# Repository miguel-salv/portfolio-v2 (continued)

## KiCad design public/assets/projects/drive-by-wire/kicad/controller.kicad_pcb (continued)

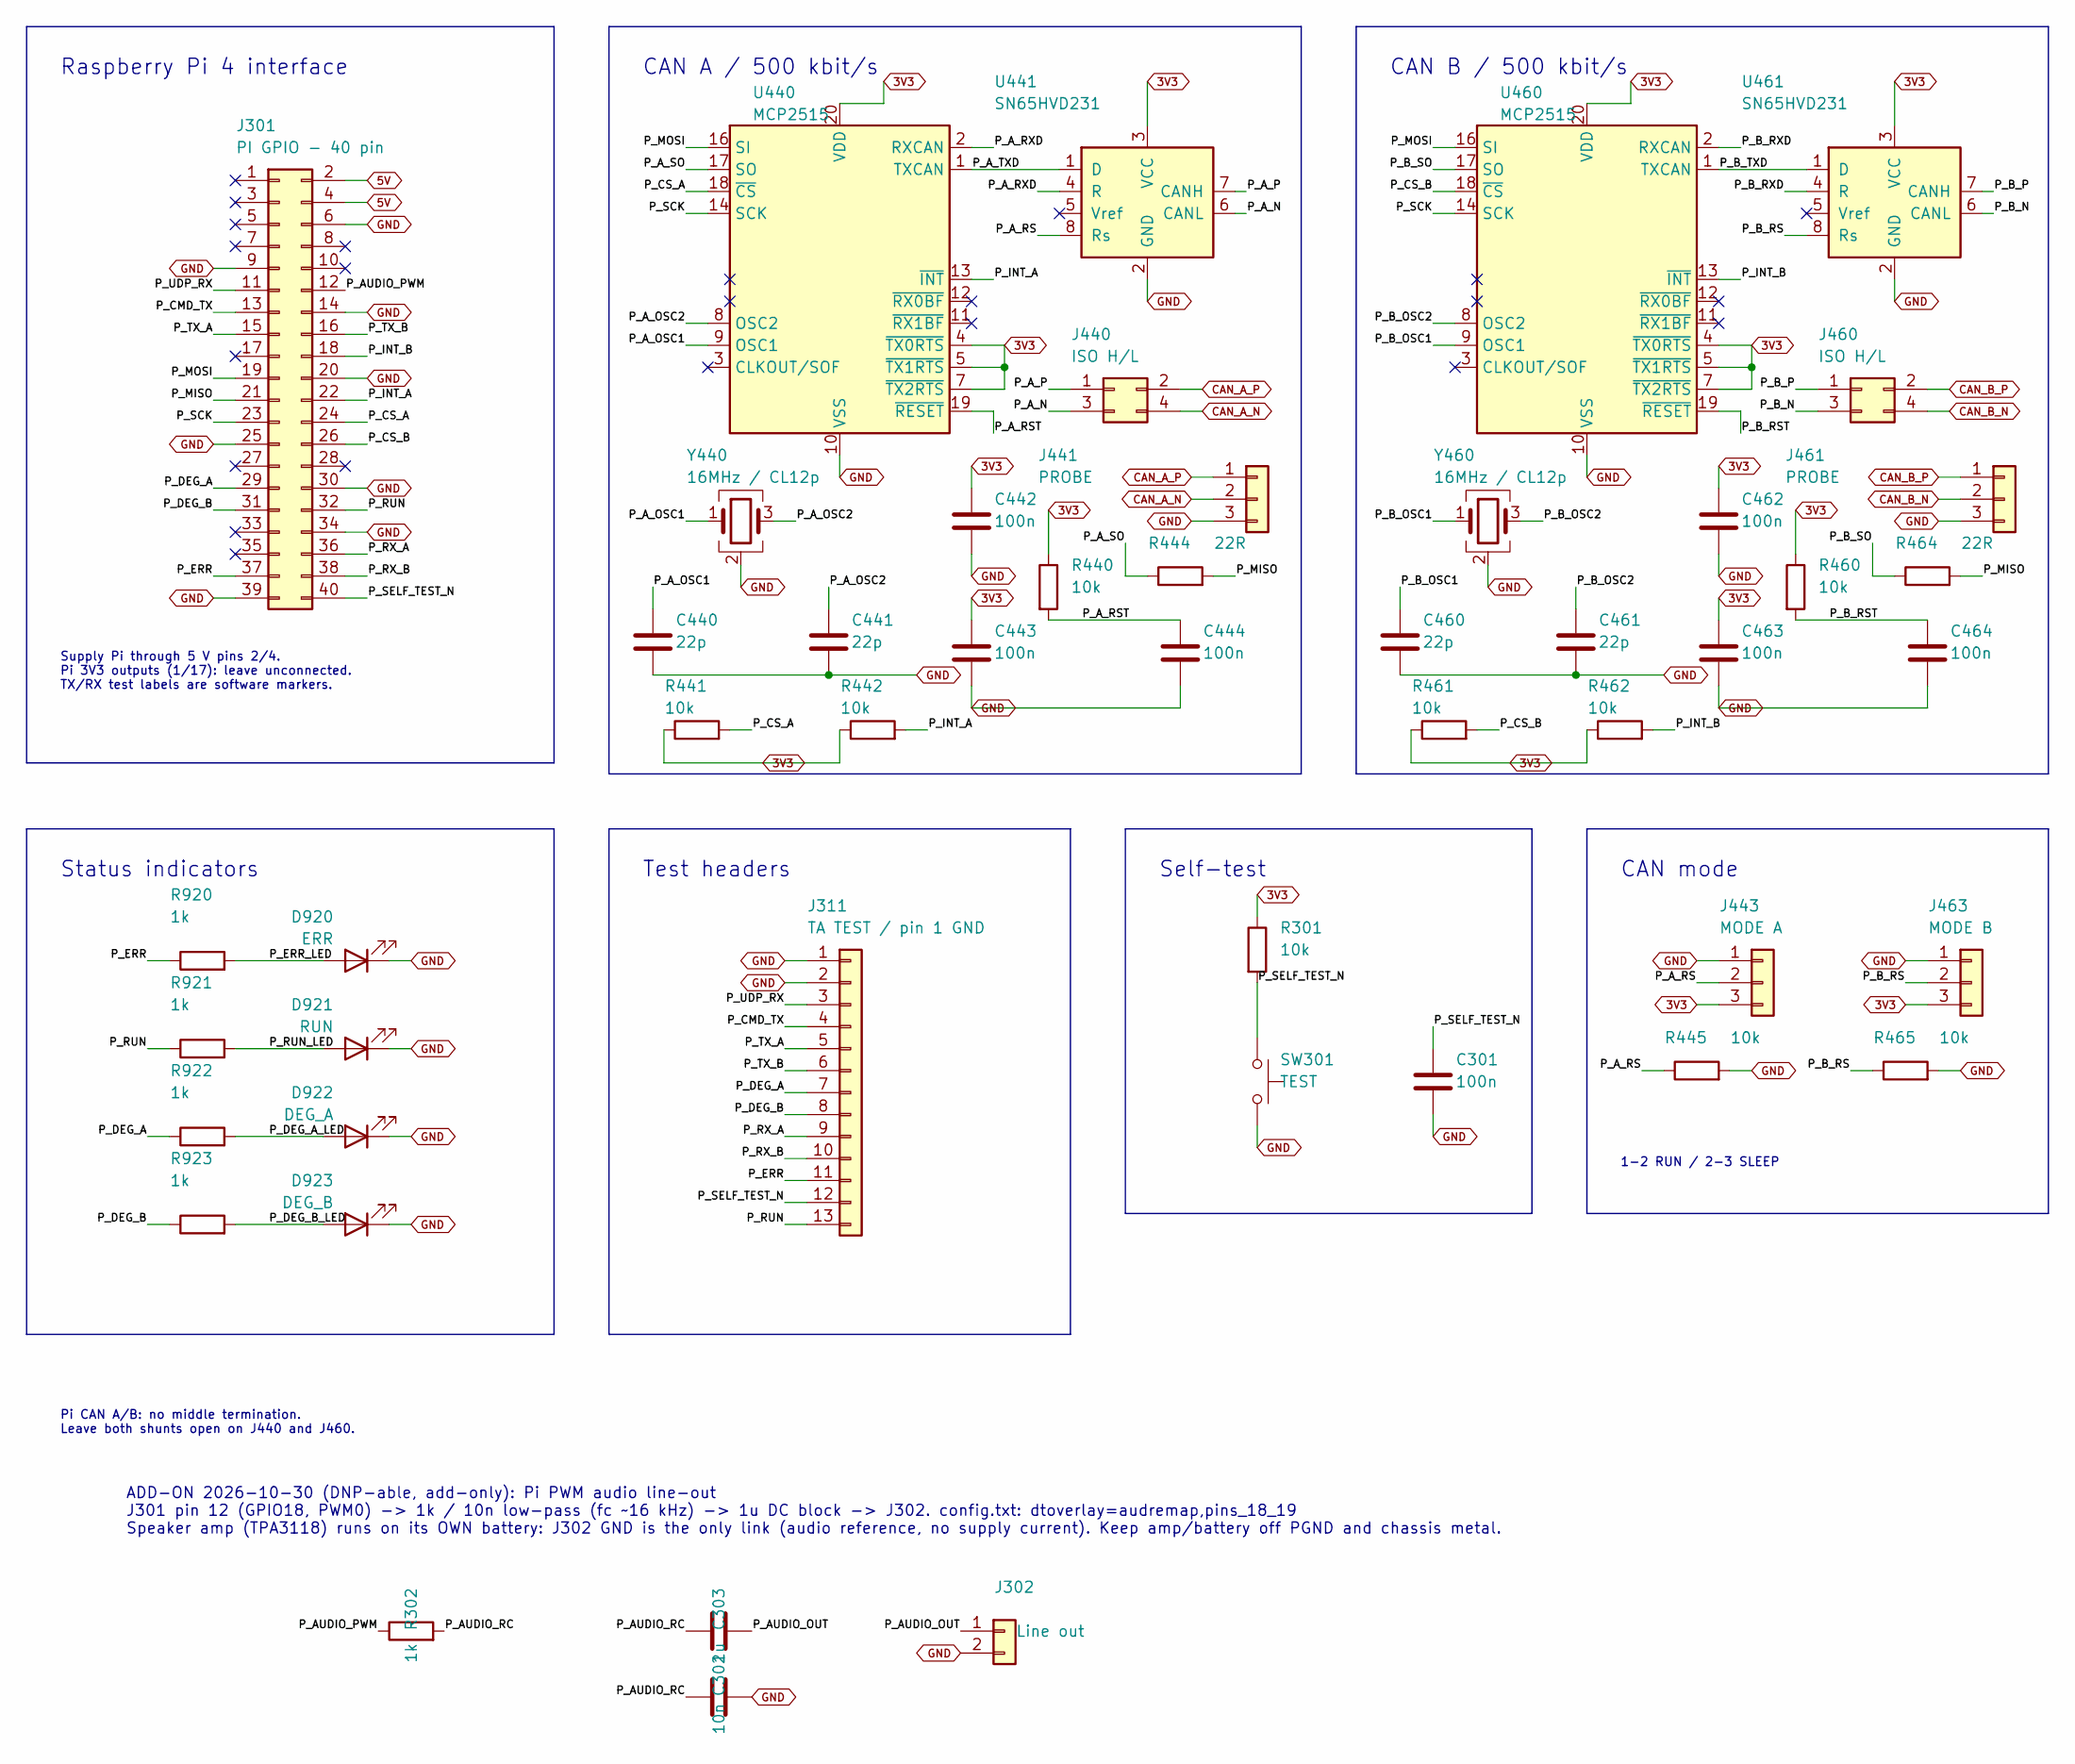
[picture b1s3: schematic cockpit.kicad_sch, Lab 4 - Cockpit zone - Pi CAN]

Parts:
C301, C442, C443, C444, C462, C463, C464: 100n; C_0603_1608Metric; Rating 100n; official v2 stock; 22u/4.7u 0805,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; MPN KGM15AR71C104KT; LCSC N/A - manual / unresolved
C302: 10n; C_0603_1608Metric; Rating PWM audio low-pass C, X7R 50 V; MPN CL10B103KB8NNNC; JLCPCB Class Verify at order
C303: 1u; C_0603_1608Metric; Rating DC block; with ~10k amp input, high-pas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; MPN CL10A105KB8NNNC; JLCPCB Class Verify at order
C440, C441, C460, C461: 22p; C_0603_1608Metric; Rating 22p; official v2 stock; 22u/4.7u 0805, 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; MPN C0603C220J1GACTU; LCSC N/A - manual / unresolved
D920: ERR; LED_0603_1608Metric; Rating 0603; green RUN / red ERR and DEG; MPN LTST-C190KRKT; LCSC N/A - manual / unresolved
D921: RUN; LED_0603_1608Metric; Rating 0603; green RUN / red ERR and DEG; MPN LTST-C190GKT; LCSC N/A - manual / unresolved
D922: DEG_A; LED_0603_1608Metric; Rating 0603; green RUN / red ERR and DEG; MPN LTST-C190KRKT; LCSC N/A - manual / unresolved
D923: DEG_B; LED_0603_1608Metric; Rating 0603; green RUN / red ERR and DEG; MPN LTST-C190KRKT; LCSC N/A - manual / unresolved
J301: PI GPIO - 40 pin; PinHeader_2x20_P2.54mm_Vertical; Rating See footprint and netlist for pin count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; MPN 2.54mm pin header; cut to length; LCSC N/A - manual / unresolved
J302: Line out; PinHeader_1x02_P2.54mm_Vertical; Rating 1 = AUDIO (to amp IN+), 2 = GND (to amp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; MPN 2.54mm pin header 1x02 (cut from strip); JLCPCB Class Verify at order
J311: TA TEST / pin 1 GND; PinHeader_1x13_P2.54mm_Vertical; Rating See footprint and netlist for pin count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; MPN 2.54mm pin header; cut to length; LCSC N/A - manual / unresolved
J440, J460: ISO H/L; PinHeader_2x02_P2.54mm_Vertical; Rating See footprint and netlist for pin count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; MPN 2.54mm pin header; cut to length; LCSC N/A - manual / unresolved
J441, J461: PROBE; PinHeader_1x03_P2.54mm_Vertical; Rating See footprint and netlist for pin count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; MPN 2.54mm pin header; cut to length; LCSC N/A - manual / unresolved
J443: MODE A; PinHeader_1x03_P2.54mm_Vertical; Rating See footprint and netlist for pin count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; MPN 2.54mm pin header; cut to length; LCSC N/A - manual / unresolved
J463: MODE B; PinHeader_1x03_P2.54mm_Vertical; Rating See footprint and netlist for pin count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; MPN 2.54mm pin header; cut to length; LCSC N/A - manual / unresolved
R301, R440, R441, R442, R445, R460, R461, R462, R465: 10k; R_0603_1608Metric; Rating 10k; 0603 0.1W; 22R 5%, others 1%; MPN CRCW060310K0FKEA; LCSC N/A - manual / unresolved
R302: 1k; R_0603_1608Metric; Rating PWM audio low-pass R (with C302: fc = 1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; MPN 0603WAF1001T5E; JLCPCB Class Verify at order
R444, R464: 22R; R_0603_1608Metric; Rating 22R; 0603 0.1W; 22R 5%, others 1%; MPN CRGCQ0603J22R; LCSC N/A - manual / unresolved
R920, R921, R922, R923: 1k; R_0603_1608Metric; Rating 1k; 0603 0.1W; 22R 5%, others 1%; MPN ERJ-3EKF1001V; LCSC N/A - manual / unresolved
SW301: TEST; SW_GCT_SWT0210; Rating Course part, custom two-net footprint v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; MPN SWT0210-045026GSA; LCSC N/A - manual / unresolved
U440, U460: MCP2515; TSSOP-20_4.4x6.5mm_P0.65mm; Rating TSSOP20; 16MHz at 3V3; MPN MCP2515T-I/ST; LCSC C185941
U441, U461: SN65HVD231; SOIC-8_3.9x4.9mm_P1.27mm; Rating SOIC8; Rs mode 1-2 RUN, 2-3 SLEEP. 10k 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; MPN SN65HVD231DR; LCSC C129257
Y440, Y460: 16MHz / CL12p; Crystal_SMD_3225-4Pin_3.2x2.5mm; Rating 16MHz CL12pF 80ohm; 3225 four pads; par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; MPN CX3225SB16000H0FLJCC; LCSC N/A - course stock

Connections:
3V3: C442.1, C443.1, C462.1, C463.1, J443.3, J463.3, R301.1, R440.1, R441.1, R442.1, R460.1, R461.1, R462.1, U440.4 (~TX0RTS), U440.5 (~TX1RTS), U440.7 (~TX2RTS), U440.20 (VDD), U441.3 (VCC), U460.4 (~TX0RTS), U460.5 (~TX1RTS), U460.7 (~TX2RTS), U460.20 (VDD), U461.3 (VCC); also elsewhere on the board
5V: J301.2, J301.4; also elsewhere on the board
/Cockpit zone - Pi CAN/P_AUDIO_OUT: C303.2, J302.1
/Cockpit zone - Pi CAN/P_AUDIO_PWM: J301.12, R302.1
/Cockpit zone - Pi CAN/P_AUDIO_RC: C302.1, C303.1, R302.2
/Cockpit zone - Pi CAN/P_A_N: J440.3, U441.6 (CANL)
/Cockpit zone - Pi CAN/P_A_OSC1: C440.1, U440.9 (OSC1), Y440.1
/Cockpit zone - Pi CAN/P_A_OSC2: C441.1, U440.8 (OSC2), Y440.3
/Cockpit zone - Pi CAN/P_A_P: J440.1, U441.7 (CANH)
/Cockpit zone - Pi CAN/P_A_RS: J443.2, R445.1, U441.8 (Rs)
/Cockpit zone - Pi CAN/P_A_RST: C444.1, R440.2, U440.19 (~RESET)
/Cockpit zone - Pi CAN/P_A_RXD: U440.2 (RXCAN), U441.4 (R)
/Cockpit zone - Pi CAN/P_A_SO: R444.1, U440.17 (SO)
/Cockpit zone - Pi CAN/P_A_TXD: U440.1 (TXCAN), U441.1 (D)
/Cockpit zone - Pi CAN/P_B_N: J460.3, U461.6 (CANL)
/Cockpit zone - Pi CAN/P_B_OSC1: C460.1, U460.9 (OSC1), Y460.1
/Cockpit zone - Pi CAN/P_B_OSC2: C461.1, U460.8 (OSC2), Y460.3
/Cockpit zone - Pi CAN/P_B_P: J460.1, U461.7 (CANH)
/Cockpit zone - Pi CAN/P_B_RS: J463.2, R465.1, U461.8 (Rs)
/Cockpit zone - Pi CAN/P_B_RST: C464.1, R460.2, U460.19 (~RESET)
/Cockpit zone - Pi CAN/P_B_RXD: U460.2 (RXCAN), U461.4 (R)
/Cockpit zone - Pi CAN/P_B_SO: R464.1, U460.17 (SO)
/Cockpit zone - Pi CAN/P_B_TXD: U460.1 (TXCAN), U461.1 (D)
/Cockpit zone - Pi CAN/P_CMD_TX: J301.13, J311.4
/Cockpit zone - Pi CAN/P_CS_A: J301.24, R441.2, U440.18 (~CS)
/Cockpit zone - Pi CAN/P_CS_B: J301.26, R461.2, U460.18 (~CS)
/Cockpit zone - Pi CAN/P_DEG_A: J301.29, J311.7, R922.1
/Cockpit zone - Pi CAN/P_DEG_A_LED: D922.2 (A), R922.2
/Cockpit zone - Pi CAN/P_DEG_B: J301.31, J311.8, R923.1
/Cockpit zone - Pi CAN/P_DEG_B_LED: D923.2 (A), R923.2
/Cockpit zone - Pi CAN/P_ERR: J301.37, J311.11, R920.1
/Cockpit zone - Pi CAN/P_ERR_LED: D920.2 (A), R920.2
/Cockpit zone - Pi CAN/P_INT_A: J301.22, R442.2, U440.13 (~INT)
/Cockpit zone - Pi CAN/P_INT_B: J301.18, R462.2, U460.13 (~INT)
/Cockpit zone - Pi CAN/P_MISO: J301.21, R444.2, R464.2
/Cockpit zone - Pi CAN/P_MOSI: J301.19, U440.16 (SI), U460.16 (SI)
/Cockpit zone - Pi CAN/P_RUN: J301.32, J311.13, R921.1
/Cockpit zone - Pi CAN/P_RUN_LED: D921.2 (A), R921.2
/Cockpit zone - Pi CAN/P_RX_A: J301.36, J311.9
/Cockpit zone - Pi CAN/P_RX_B: J301.38, J311.10
/Cockpit zone - Pi CAN/P_SCK: J301.23, U440.14 (SCK), U460.14 (SCK)
/Cockpit zone - Pi CAN/P_SELF_TEST_N: C301.1, J301.40, J311.12, R301.2, SW301.1
/Cockpit zone - Pi CAN/P_TX_A: J301.15, J311.5
/Cockpit zone - Pi CAN/P_TX_B: J301.16, J311.6
/Cockpit zone - Pi CAN/P_UDP_RX: J301.11, J311.3
CAN_A_N: J440.4, J441.2; also elsewhere on the board
CAN_A_P: J440.2, J441.1; also elsewhere on the board
CAN_B_N: J460.4, J461.2; also elsewhere on the board
CAN_B_P: J460.2, J461.1; also elsewhere on the board
GND: C301.2, C302.2, C440.2, C441.2, C442.2, C443.2, C444.2, C460.2, C461.2, C462.2, C463.2, C464.2, D920.1 (K), D921.1 (K), D922.1 (K), D923.1 (K), J301.6, J301.9, J301.14, J301.20, J301.25, J301.30, J301.34, J301.39, J302.2, J311.1, J311.2, J441.3, J443.1, J461.3, J463.1, R445.2, R465.2, SW301.2, U440.10 (VSS), U441.2 (GND), U460.10 (VSS), U461.2 (GND), Y440.2 (G), Y440.4 (G), Y460.2 (G), Y460.4 (G); also elsewhere on the board

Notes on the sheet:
Test headers
CAN A / 500 kbit/s
Pi CAN A/B: no middle termination. Leave both shunts open on J440 and J460.
1-2 RUN / 2-3 SLEEP
CAN mode
Status indicators
CAN B / 500 kbit/s
Supply Pi through 5 V pins 2/4. Pi 3V3 outputs (1/17): leave unconnected. TX/RX test labels are software markers.
Self-test
Raspberry Pi 4 interface
ADD-ON 2026-10-30 (DNP-able, add-only): Pi PWM audio line-out J301 pin 12 (GPIO18, PWM0) -> 1k / 10n low-pass (fc ~16 kHz) -> 1u DC block -> J302. config.txt: dtoverlay=audremap,pins_18_19 Speaker amp (TPA3118) runs on its OWN battery: J302 GND is the only link (audio reference, no supply current).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

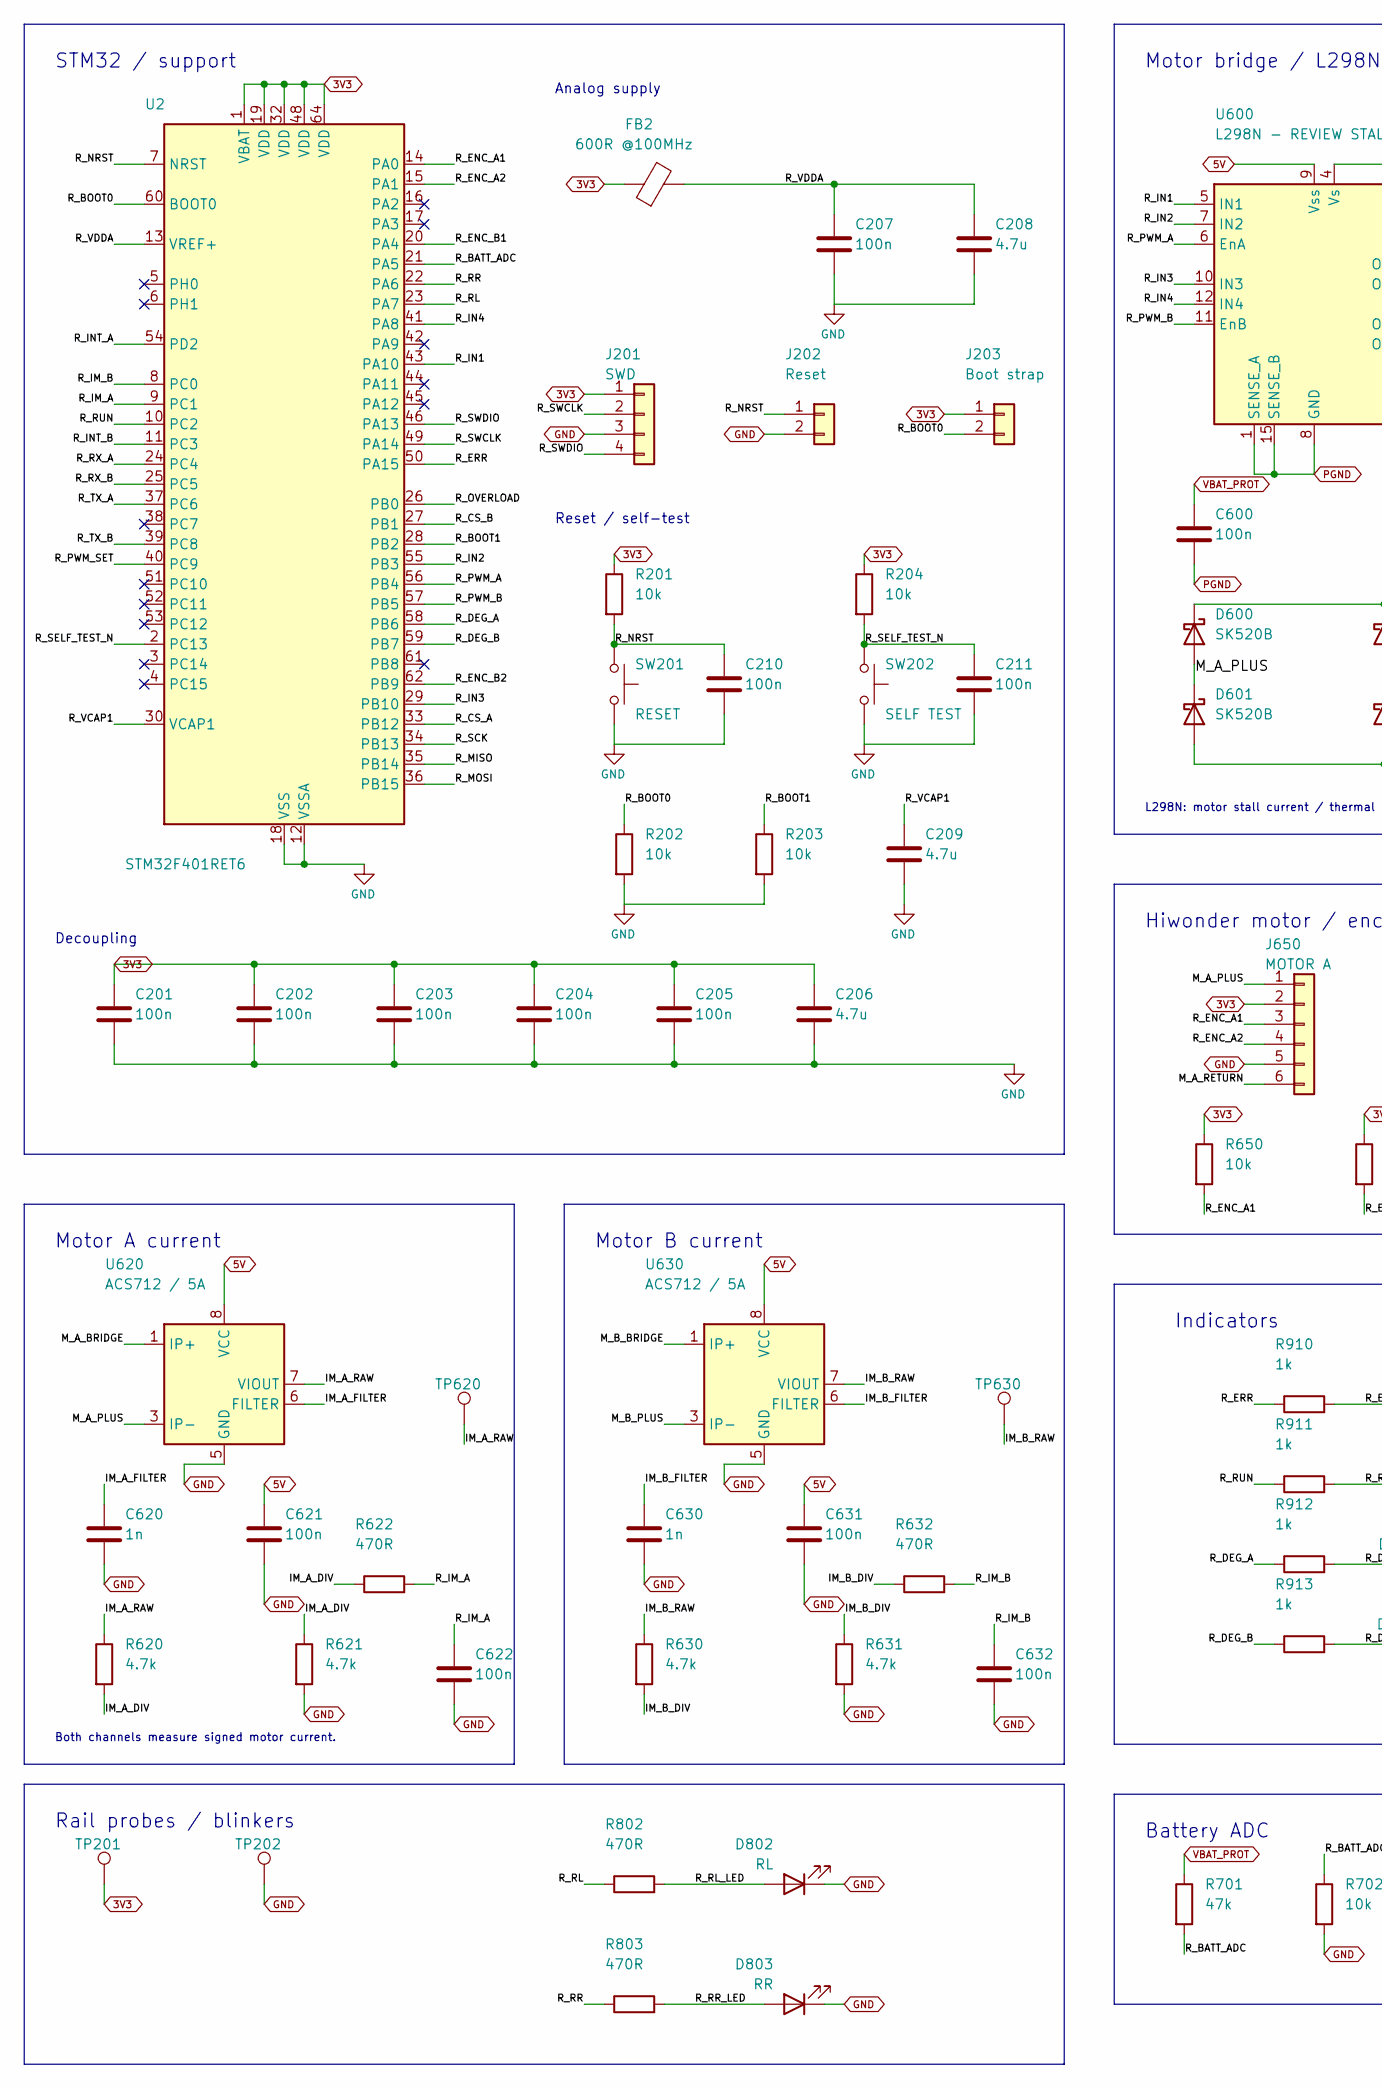
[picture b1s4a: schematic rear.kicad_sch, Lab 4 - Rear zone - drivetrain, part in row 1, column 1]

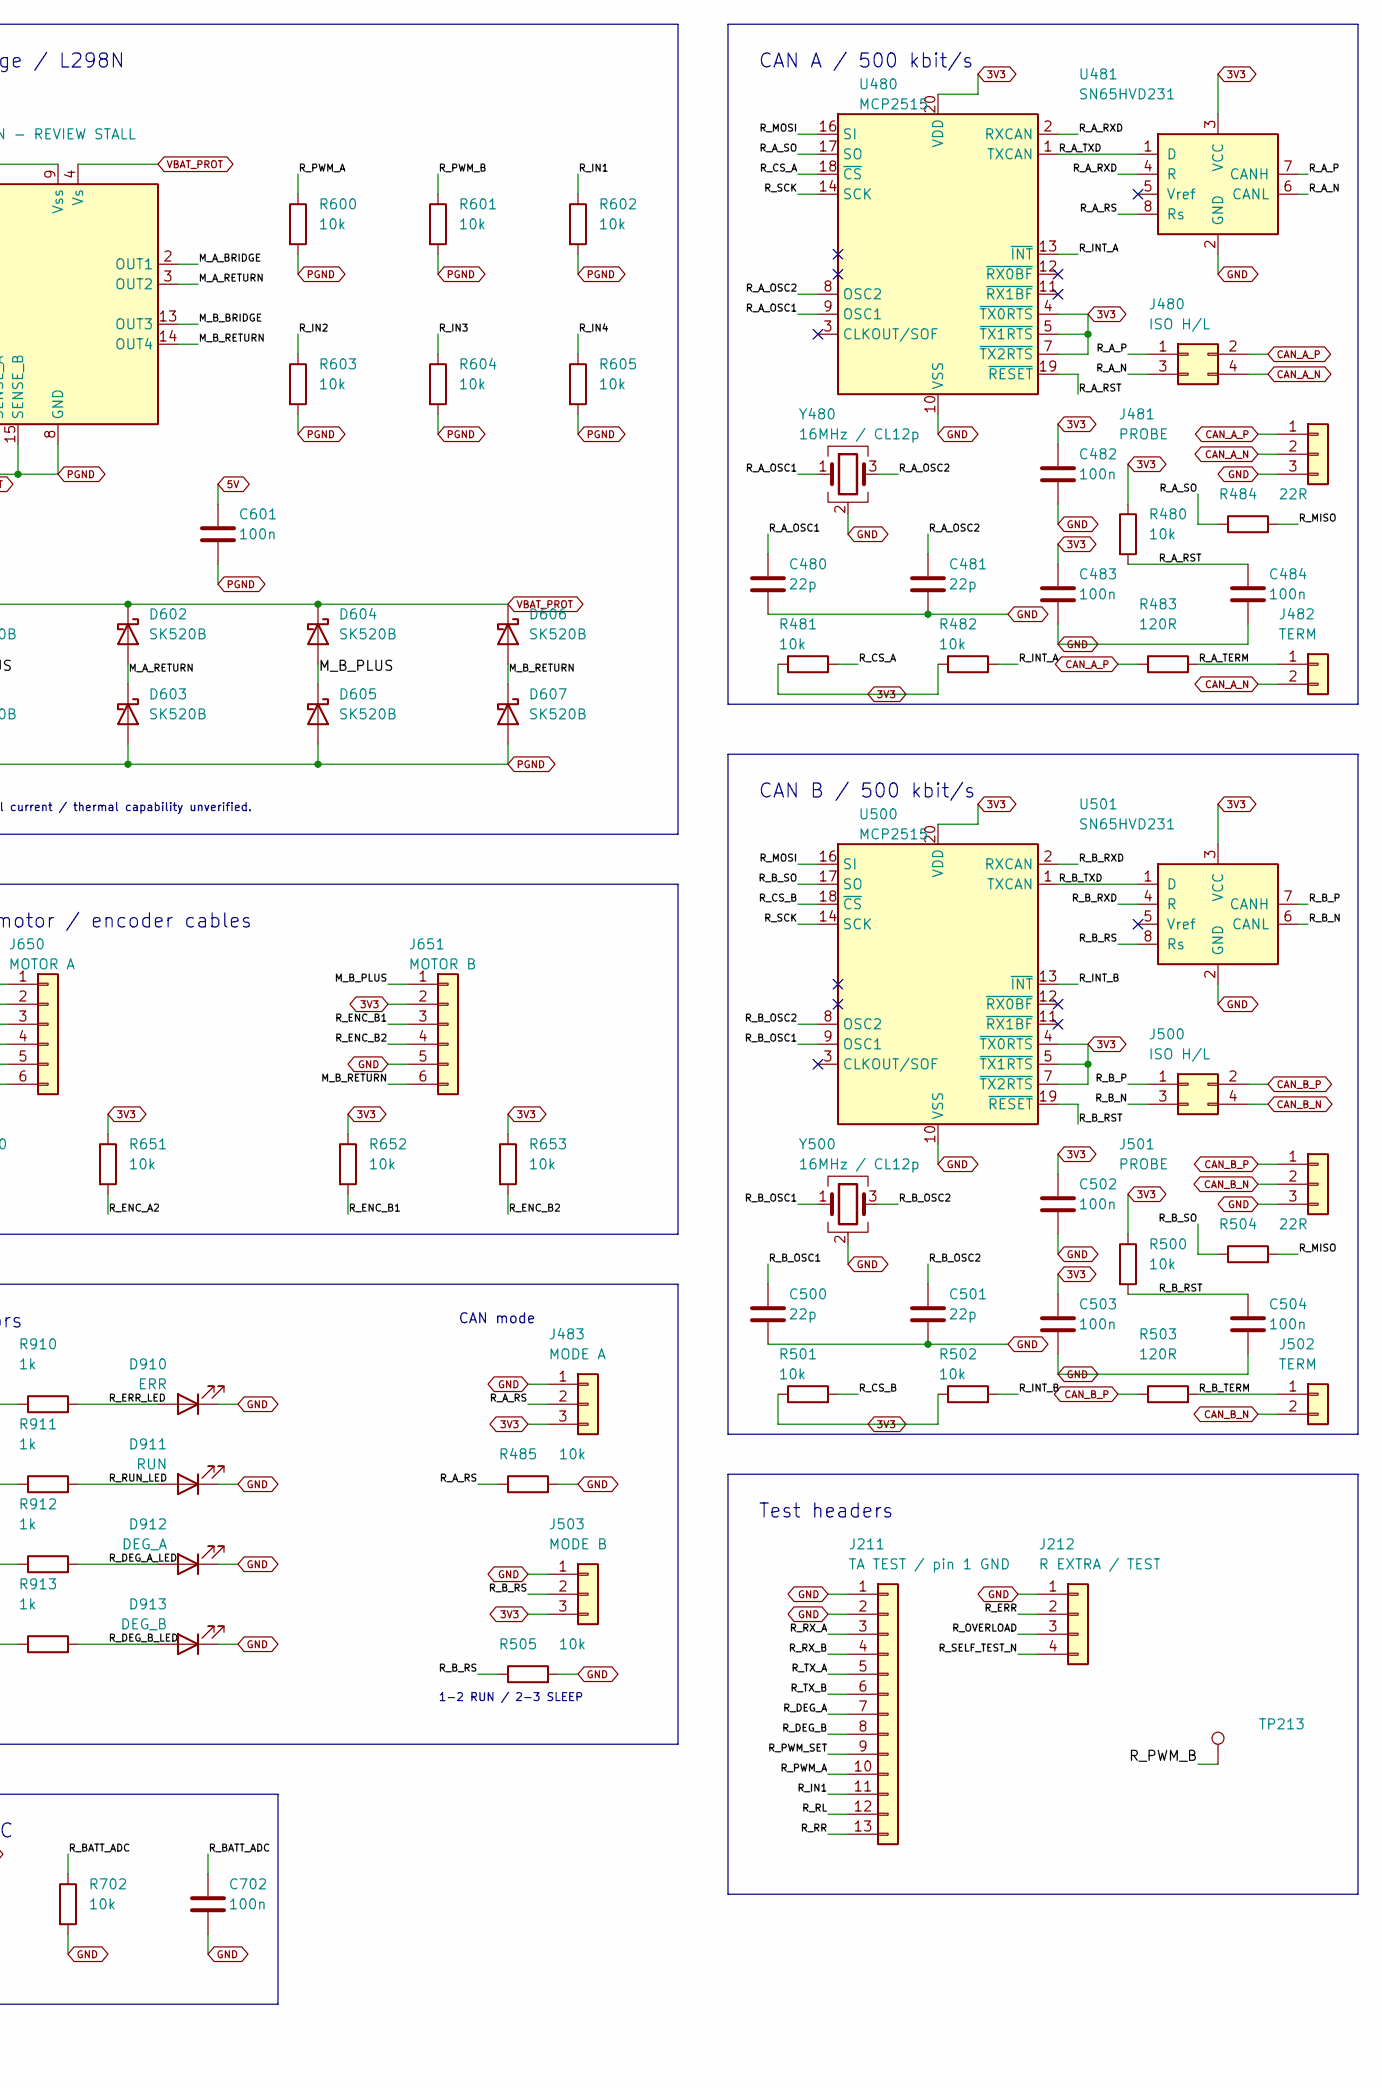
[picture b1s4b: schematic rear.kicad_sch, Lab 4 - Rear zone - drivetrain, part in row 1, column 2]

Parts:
C201, C202, C203, C204, C205, C207, C210, C211, C482, C483, C484, C502, C503, C504, C600, C601, C621, C622, C631, C632, C702: 100n; C_0603_1608Metric; Rating 100n; official v2 stock; 22u/4.7u 0805,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; MPN KGM15AR71C104KT; LCSC N/A - manual / unresolved
C206, C208, C209: 4.7u; C_0805_2012Metric; Rating 4.7u; official v2 stock; 22u/4.7u 0805,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; MPN GRM21BR71C475KE51L; LCSC N/A - manual / unresolved
C480, C481, C500, C501: 22p; C_0603_1608Metric; Rating 22p; official v2 stock; 22u/4.7u 0805, 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; MPN C0603C220J1GACTU; LCSC N/A - manual / unresolved
C620, C630: 1n; C_0603_1608Metric; Rating 1n; official v2 stock; 22u/4.7u 0805, o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; MPN GCM1885C2A102FA16D; LCSC N/A - manual / unresolved
D600, D601, D602, D603, D604, D605, D606, D607: SK520B; D_SMB; Rating 5A 200V SMB; bridge flyback; MPN SK520B; LCSC N/A - manual / unresolved
D802: RL; LED_D3.0mm; Rating Yellow 3mm radial; 470R limits current; MPN 151031YS06000; LCSC N/A - manual / unresolved
D803: RR; LED_D3.0mm; Rating Yellow 3mm radial; 470R limits current; MPN 151031YS06000; LCSC N/A - manual / unresolved
D910: ERR; LED_0603_1608Metric; Rating 0603; green RUN / red ERR and DEG; MPN LTST-C190KRKT; LCSC N/A - manual / unresolved
D911: RUN; LED_0603_1608Metric; Rating 0603; green RUN / red ERR and DEG; MPN LTST-C190GKT; LCSC N/A - manual / unresolved
D912: DEG_A; LED_0603_1608Metric; Rating 0603; green RUN / red ERR and DEG; MPN LTST-C190KRKT; LCSC N/A - manual / unresolved
D913: DEG_B; LED_0603_1608Metric; Rating 0603; green RUN / red ERR and DEG; MPN LTST-C190KRKT; LCSC N/A - manual / unresolved
FB2: 600R @100MHz; L_0603_1608Metric; Rating 0603; 600ohm@100MHz,500mA; 0.35ohm maxD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; MPN 742863160; LCSC N/A - manual / unresolved
J201: SWD; PinHeader_1x04_P2.54mm_Vertical; Rating See footprint and netlist for pin count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; MPN 2.54mm pin header; cut to length; LCSC N/A - manual / unresolved
J202: Reset; PinHeader_1x02_P2.54mm_Vertical; Rating See footprint and netlist for pin count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; MPN 2.54mm pin header; cut to length; LCSC N/A - manual / unresolved
J203: Boot strap; PinHeader_1x02_P2.54mm_Vertical; Rating See footprint and netlist for pin count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; MPN 2.54mm pin header; cut to length; LCSC N/A - manual / unresolved
J211: TA TEST / pin 1 GND; PinHeader_1x13_P2.54mm_Vertical; Rating See footprint and netlist for pin count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; MPN 2.54mm pin header; cut to length; LCSC N/A - manual / unresolved
J212: R EXTRA / TEST; PinHeader_1x04_P2.54mm_Vertical; Rating See footprint and netlist for pin count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; MPN 2.54mm pin header; cut to length; LCSC N/A - manual / unresolved
J480, J500: ISO H/L; PinHeader_2x02_P2.54mm_Vertical; Rating See footprint and netlist for pin count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; MPN 2.54mm pin header; cut to length; LCSC N/A - manual / unresolved
J481, J501: PROBE; PinHeader_1x03_P2.54mm_Vertical; Rating See footprint and netlist for pin count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; MPN 2.54mm pin header; cut to length; LCSC N/A - manual / unresolved
J482, J502: TERM; PinHeader_1x02_P2.54mm_Vertical; Rating See footprint and netlist for pin count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; MPN 2.54mm pin header; cut to length; LCSC N/A - manual / unresolved
J483: MODE A; PinHeader_1x03_P2.54mm_Vertical; Rating See footprint and netlist for pin count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; MPN 2.54mm pin header; cut to length; LCSC N/A - manual / unresolved
J503: MODE B; PinHeader_1x03_P2.54mm_Vertical; Rating See footprint and netlist for pin count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; MPN 2.54mm pin header; cut to length; LCSC N/A - manual / unresolved
J650: MOTOR A; JST_PH_B6B-PH-SM4-TB_1x06-1MP_P2.00mm_Vertical; Rating PH2.0 six-pin; 1=M+,2=encoder3V3,3=A,4=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; MPN B6B-PH-SM4-TB; LCSC N/A - manual / unresolved
J651: MOTOR B; JST_PH_B6B-PH-SM4-TB_1x06-1MP_P2.00mm_Vertical; Rating PH2.0 six-pin; 1=M+,2=encoder3V3,3=A,4=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; MPN B6B-PH-SM4-TB; LCSC N/A - manual / unresolved
R201, R202, R203, R204, R480, R481, R482, R485, R500, R501, R502, R505, R600, R601, R602, R603, R604, R605, R650, R651, R652, R653, R702: 10k; R_0603_1608Metric; Rating 10k; 0603 0.1W; 22R 5%, others 1%; MPN CRCW060310K0FKEA; LCSC N/A - manual / unresolved
R483, R503: 120R; R_0603_1608Metric; Rating 120R; 0603 0.1W; 22R 5%, others 1%; MPN RC0603FR-07120RL; LCSC N/A - manual / unresolved
R484, R504: 22R; R_0603_1608Metric; Rating 22R; 0603 0.1W; 22R 5%, others 1%; MPN CRGCQ0603J22R; LCSC N/A - manual / unresolved
R620, R621, R630, R631: 4.7k; R_0603_1608Metric; Rating 4.7k; 0603 0.1W; 22R 5%, others 1%; MPN RC0603FR-074K7L; LCSC N/A - manual / unresolved
R622, R632, R802, R803: 470R; R_0603_1608Metric; Rating 470R; 0603 0.1W; 22R 5%, others 1%; MPN RC0603FR-07470RL; LCSC N/A - manual / unresolved
R701: 47k; R_0603_1608Metric; Rating 47k; 0603 0.1W; 22R 5%, others 1%; MPN RC0603FR-0747KL; LCSC N/A - manual / unresolved
R910, R911, R912, R913: 1k; R_0603_1608Metric; Rating 1k; 0603 0.1W; 22R 5%, others 1%; MPN ERJ-3EKF1001V; LCSC N/A - manual / unresolved
SW201: RESET; SW_GCT_SWT0210; Rating Course part, custom two-net footprint v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; MPN SWT0210-045026GSA; LCSC N/A - manual / unresolved
SW202: SELF TEST; SW_GCT_SWT0210; Rating Course part, custom two-net footprint v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; MPN SWT0210-045026GSA; LCSC N/A - manual / unresolved
TP201: 3V3; PinHeader_1x01_P2.54mm_Vertical; Rating 1-pin through-hole probe header, 2.54mm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; MPN 2.54mm pin header; cut to 1 pin; LCSC N/A - manual / unresolved
TP202: GND; PinHeader_1x01_P2.54mm_Vertical; Rating 1-pin through-hole probe header, 2.54mm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; MPN 2.54mm pin header; cut to 1 pin; LCSC N/A - manual / unresolved
TP213: R_PWM_B; PinHeader_1x01_P2.54mm_Vertical; Rating 1-pin through-hole PWM_B probe header; MPN 2.54mm pin header; cut to 1 pin; LCSC N/A - manual / unresolved
TP620: IM_A_RAW; PinHeader_1x01_P2.54mm_Vertical; Rating 1-pin through-hole probe header, 2.54mm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; MPN 2.54mm pin header; cut to 1 pin; LCSC N/A - manual / unresolved
TP630: IM_B_RAW; PinHeader_1x01_P2.54mm_Vertical; Rating 1-pin through-hole probe header, 2.54mm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; MPN 2.54mm pin header; cut to 1 pin; LCSC N/A - manual / unresolved
U2: STM32F401RET6; LQFP-64_10x10mm_P0.5mm; Rating LQFP64, bare MCU; TR tape/reel suffix; MPN STM32F401RET6TR; LCSC N/A - manual / unresolved
U480, U500: MCP2515; TSSOP-20_4.4x6.5mm_P0.65mm; Rating TSSOP20; 16MHz at 3V3; MPN MCP2515T-I/ST; LCSC C185941
U481, U501: SN65HVD231; SOIC-8_3.9x4.9mm_P1.27mm; Rating SOIC8; Rs mode 1-2 RUN, 2-3 SLEEP. 10k 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; MPN SN65HVD231DR; LCSC C129257
U600: L298N - REVIEW STALL; L298N_Multiwatt15_HeatsinkReserve; Rating Multiwatt15; 2A DC/channel ceiling, no 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; MPN L298N; LCSC N/A - manual / unresolved
U620, U630: ACS712 / 5A; SOIC-8_3.9x4.9mm_P1.27mm; Rating SOIC8; +/-5A; 185mV/A; 5V supply; MPN ACS712ELCTR-05B-T; LCSC C44471
Y480, Y500: 16MHz / CL12p; Crystal_SMD_3225-4Pin_3.2x2.5mm; Rating 16MHz CL12pF 80ohm; 3225 four pads; par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; MPN CX3225SB16000H0FLJCC; LCSC N/A - course stock

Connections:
3V3: C201.1, C202.1, C203.1, C204.1, C205.1, C206.1, C482.1, C483.1, C502.1, C503.1, FB2.1, J201.1, J203.1, J483.3, J503.3, J650.2, J651.2, R201.1, R204.1, R480.1, R481.1, R482.1, R500.1, R501.1, R502.1, R650.1, R651.1, R652.1, R653.1, TP201.1 (1_1), U2.1 (VBAT), U2.19 (VDD), U2.32 (VDD), U2.48 (VDD), U2.64 (VDD), U480.4 (~TX0RTS), U480.5 (~TX1RTS), U480.7 (~TX2RTS), U480.20 (VDD), U481.3 (VCC), U500.4 (~TX0RTS), U500.5 (~TX1RTS), U500.7 (~TX2RTS), U500.20 (VDD), U501.3 (VCC); also elsewhere on the board
5V: C601.1, C621.1, C631.1, U600.9 (Vss), U620.8 (VCC), U630.8 (VCC); also elsewhere on the board
/Rear zone - drivetrain/IM_A_DIV: R620.2, R621.1, R622.1
/Rear zone - drivetrain/IM_A_FILTER: C620.1, U620.6 (FILTER)
/Rear zone - drivetrain/IM_A_RAW: R620.1, TP620.1 (1_1), U620.7 (VIOUT)
/Rear zone - drivetrain/IM_B_DIV: R630.2, R631.1, R632.1
/Rear zone - drivetrain/IM_B_FILTER: C630.1, U630.6 (FILTER)
/Rear zone - drivetrain/IM_B_RAW: R630.1, TP630.1 (1_1), U630.7 (VIOUT)
/Rear zone - drivetrain/M_A_BRIDGE: U600.2 (OUT1), U620.1 (IP+), U620.2 (IP+)
/Rear zone - drivetrain/M_A_PLUS: D600.2 (A), D601.1 (K), J650.1, U620.3 (IP-), U620.4 (IP-)
/Rear zone - drivetrain/M_A_RETURN: D602.2 (A), D603.1 (K), J650.6, U600.3 (OUT2)
/Rear zone - drivetrain/M_B_BRIDGE: U600.13 (OUT3), U630.1 (IP+), U630.2 (IP+)
/Rear zone - drivetrain/M_B_PLUS: D604.2 (A), D605.1 (K), J651.1, U630.3 (IP-), U630.4 (IP-)
/Rear zone - drivetrain/M_B_RETURN: D606.2 (A), D607.1 (K), J651.6, U600.14 (OUT4)
/Rear zone - drivetrain/R_A_N: J480.3, U481.6 (CANL)
/Rear zone - drivetrain/R_A_OSC1: C480.1, U480.9 (OSC1), Y480.1
/Rear zone - drivetrain/R_A_OSC2: C481.1, U480.8 (OSC2), Y480.3
/Rear zone - drivetrain/R_A_P: J480.1, U481.7 (CANH)
/Rear zone - drivetrain/R_A_RS: J483.2, R485.1, U481.8 (Rs)
/Rear zone - drivetrain/R_A_RST: C484.1, R480.2, U480.19 (~RESET)
/Rear zone - drivetrain/R_A_RXD: U480.2 (RXCAN), U481.4 (R)
/Rear zone - drivetrain/R_A_SO: R484.1, U480.17 (SO)
/Rear zone - drivetrain/R_A_TERM: J482.1, R483.2
/Rear zone - drivetrain/R_A_TXD: U480.1 (TXCAN), U481.1 (D)
/Rear zone - drivetrain/R_BATT_ADC: C702.1, R701.2, R702.1, U2.21 (PA5)
/Rear zone - drivetrain/R_BOOT0: J203.2, R202.1, U2.60 (BOOT0)
/Rear zone - drivetrain/R_BOOT1: R203.1, U2.28 (PB2)
/Rear zone - drivetrain/R_B_N: J500.3, U501.6 (CANL)
/Rear zone - drivetrain/R_B_OSC1: C500.1, U500.9 (OSC1), Y500.1
/Rear zone - drivetrain/R_B_OSC2: C501.1, U500.8 (OSC2), Y500.3
/Rear zone - drivetrain/R_B_P: J500.1, U501.7 (CANH)
/Rear zone - drivetrain/R_B_RS: J503.2, R505.1, U501.8 (Rs)
/Rear zone - drivetrain/R_B_RST: C504.1, R500.2, U500.19 (~RESET)
/Rear zone - drivetrain/R_B_RXD: U500.2 (RXCAN), U501.4 (R)
/Rear zone - drivetrain/R_B_SO: R504.1, U500.17 (SO)
/Rear zone - drivetrain/R_B_TERM: J502.1, R503.2
/Rear zone - drivetrain/R_B_TXD: U500.1 (TXCAN), U501.1 (D)
/Rear zone - drivetrain/R_CS_A: R481.2, U2.33 (PB12), U480.18 (~CS)
/Rear zone - drivetrain/R_CS_B: R501.2, U2.27 (PB1), U500.18 (~CS)
/Rear zone - drivetrain/R_DEG_A: J211.7, R912.1, U2.58 (PB6)
/Rear zone - drivetrain/R_DEG_A_LED: D912.2 (A), R912.2
/Rear zone - drivetrain/R_DEG_B: J211.8, R913.1, U2.59 (PB7)
/Rear zone - drivetrain/R_DEG_B_LED: D913.2 (A), R913.2
/Rear zone - drivetrain/R_ENC_A1: J650.3, R650.2, U2.14 (PA0)
/Rear zone - drivetrain/R_ENC_A2: J650.4, R651.2, U2.15 (PA1)
/Rear zone - drivetrain/R_ENC_B1: J651.3, R652.2, U2.20 (PA4)
/Rear zone - drivetrain/R_ENC_B2: J651.4, R653.2, U2.62 (PB9)
/Rear zone - drivetrain/R_ERR: J212.2, R910.1, U2.50 (PA15)
/Rear zone - drivetrain/R_ERR_LED: D910.2 (A), R910.2
/Rear zone - drivetrain/R_IM_A: C622.1, R622.2, U2.9 (PC1)
/Rear zone - drivetrain/R_IM_B: C632.1, R632.2, U2.8 (PC0)
/Rear zone - drivetrain/R_IN1: J211.11, R602.1, U2.43 (PA10), U600.5 (IN1)
/Rear zone - drivetrain/R_IN2: R603.1, U2.55 (PB3), U600.7 (IN2)
/Rear zone - drivetrain/R_IN3: R604.1, U2.29 (PB10), U600.10 (IN3)
/Rear zone - drivetrain/R_IN4: R605.1, U2.41 (PA8), U600.12 (IN4)
/Rear zone - drivetrain/R_INT_A: R482.2, U2.54 (PD2), U480.13 (~INT)
/Rear zone - drivetrain/R_INT_B: R502.2, U2.11 (PC3), U500.13 (~INT)
/Rear zone - drivetrain/R_MISO: R484.2, R504.2, U2.35 (PB14)
/Rear zone - drivetrain/R_MOSI: U2.36 (PB15), U480.16 (SI), U500.16 (SI)
/Rear zone - drivetrain/R_NRST: C210.1, J202.1, R201.2, SW201.1, U2.7 (NRST)
/Rear zone - drivetrain/R_OVERLOAD: J212.3, U2.26 (PB0)
/Rear zone - drivetrain/R_PWM_A: J211.10, R600.1, U2.56 (PB4), U600.6 (EnA)
/Rear zone - drivetrain/R_PWM_B: R601.1, TP213.1 (1_1), U2.57 (PB5), U600.11 (EnB)
/Rear zone - drivetrain/R_PWM_SET: J211.9, U2.40 (PC9)
/Rear zone - drivetrain/R_RL: J211.12, R802.1, U2.23 (PA7)
/Rear zone - drivetrain/R_RL_LED: D802.2 (A), R802.2
/Rear zone - drivetrain/R_RR: J211.13, R803.1, U2.22 (PA6)
/Rear zone - drivetrain/R_RR_LED: D803.2 (A), R803.2
/Rear zone - drivetrain/R_RUN: R911.1, U2.10 (PC2)
/Rear zone - drivetrain/R_RUN_LED: D911.2 (A), R911.2
/Rear zone - drivetrain/R_RX_A: J211.3, U2.24 (PC4)
/Rear zone - drivetrain/R_RX_B: J211.4, U2.25 (PC5)
/Rear zone - drivetrain/R_SCK: U2.34 (PB13), U480.14 (SCK), U500.14 (SCK)
/Rear zone - drivetrain/R_SELF_TEST_N: C211.1, J212.4, R204.2, SW202.1, U2.2 (PC13)
/Rear zone - drivetrain/R_SWCLK: J201.2, U2.49 (PA14)
/Rear zone - drivetrain/R_SWDIO: J201.4, U2.46 (PA13)
/Rear zone - drivetrain/R_TX_A: J211.5, U2.37 (PC6)
/Rear zone - drivetrain/R_TX_B: J211.6, U2.39 (PC8)
/Rear zone - drivetrain/R_VCAP1: C209.1, U2.30 (VCAP1)
/Rear zone - drivetrain/R_VDDA: C207.1, C208.1, FB2.2, U2.13 (VREF+)
CAN_A_N: J480.4, J481.2, J482.2; also elsewhere on the board
CAN_A_P: J480.2, J481.1, R483.1; also elsewhere on the board
CAN_B_N: J500.4, J501.2, J502.2; also elsewhere on the board
CAN_B_P: J500.2, J501.1, R503.1; also elsewhere on the board
GND: C201.2, C202.2, C203.2, C204.2, C205.2, C206.2, C207.2, C208.2, C209.2, C210.2, C211.2, C480.2, C481.2, C482.2, C483.2, C484.2, C500.2, C501.2, C502.2, C503.2, C504.2, C620.2, C621.2, C622.2, C630.2, C631.2, C632.2, C702.2, D802.1 (K), D803.1 (K), D910.1 (K), D911.1 (K), D912.1 (K), D913.1 (K), J201.3, J202.2, J211.1, J211.2, J212.1, J481.3, J483.1, J501.3, J503.1, J650.5, J651.5, R202.2, R203.2, R485.2, R505.2, R621.2, R631.2, R702.2, SW201.2, SW202.2, TP202.1 (1_1), U2.12 (VSSA), U2.18 (VSS), U2.31 (VSS), U2.47 (VSS), U2.63 (VSS), U480.10 (VSS), U481.2 (GND), U500.10 (VSS), U501.2 (GND), U620.5 (GND), U630.5 (GND), Y480.2 (G), Y480.4 (G), Y500.2 (G), Y500.4 (G); also elsewhere on the board
PGND: C600.2, C601.2, D601.2 (A), D603.2 (A), D605.2 (A), D607.2 (A), R600.2, R601.2, R602.2, R603.2, R604.2, R605.2, U600.1 (SENSE_A), U600.8 (GND), U600.15 (SENSE_B); also elsewhere on the board
VBAT_PROT: C600.1, D600.1 (K), D602.1 (K), D604.1 (K), D606.1 (K), R701.1, U600.4 (Vs); also elsewhere on the board

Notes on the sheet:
L298N: motor stall current / thermal capability unverified.
CAN B / 500 kbit/s
Motor bridge / L298N
Motor B current
Both channels measure signed motor current.
Rail probes / blinkers
Test headers
CAN A / 500 kbit/s
CAN mode
Battery ADC
Hiwonder motor / encoder cables
Motor A current
Reset / self-test
1-2 RUN / 2-3 SLEEP
Decoupling
Analog supply
STM32 / support
Indicators
